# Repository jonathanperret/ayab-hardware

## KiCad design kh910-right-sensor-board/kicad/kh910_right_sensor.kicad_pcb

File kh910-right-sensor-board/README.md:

# KH-910 right-hand sensor board (BP-111025-7 / PCB-E-144)

Reverse-engineering workspace for the Brother KH-910 right sensor board
(3 optical encoders via photo-interrupters PI1/PI2, hall-sensor amplifier
IC303 + comparator, mylar-reader signal conditioning).

- `tracer/` — local interactive tracing tool. Run `python3 tracer/server.py`
  and open http://localhost:8765/. All work is in `tracer/state.json`
  (pads with positions on both photos, traces with side + corners, parts);
  every save keeps a copy in `tracer/backups/`.
- `photos/` — original photos: both sides, crack close-ups, repairs, S-5 connector.
- `images/` — annotated photos, crack/repair maps; `tests/` = continuity-test probe maps.
- `kicad/` — KiCad 10 project. The schematic is the same drawing as `schematic/` (converted element by element by `kicad/build/svg_to_kicad_sch.py`) and its connectivity is checked against the tracer netlist on every build; the PCB uses the tracer's pad positions and tracks (rounded corners), with nets named as in the schematic. `kicad/build/build.sh` regenerates both (needs a python with numpy, scipy and schemdraw: `PYTHON=... kicad/build/build.sh`) and writes `erc_report.txt` / `drc_report.txt`.
- `schematic/` — schematic sheets drawn from the tracer netlist (`draw_schematic.py`), `netlist.txt` at the top level.

## Measured so far (multimeter)
- Harness pad I = +5V, H = GND; D = IC302 p13, E = IC301 p14, F = IC301 p7, G = IC301 p8.
- Bottom harness, two bundles: optical (mylar reader) board on J signal, K GND, L +5V;
  hall sensor board on M +5V, N and P outputs (difference amplifier IC303 via R335/R334), O GND.
- Open solder jumpers (solder side): JP1 between R325.1 and R326.1, JP2 between R323.1 and R324.1.
- Flex cracks repaired 2026-11-15: R1 solder-side GND bus (top edge), R2 +5V
  trace under IC302, R3a/b right-edge +5V trace (both sides), R4 solder jumper.

## To beep when the board is back
- R305.1 ↔ IC301.11 (expect beep: component-side right-edge trace = GND, drawn on that assumption)
- R305.1 ↔ IC301.4 (expect open)
- pad I ↔ IC302.2 (expect open; +5V should be on IC302.3)
- IC301 (324) pins 1, 2, 3, 6, 13 have no solder-side copper; their connections run under the IC body (component side). Beep:
  IC301.6 ↔ IC301.9, IC301.13 ↔ IC301.9 (shared comparator reference?), IC301.1 ↔ IC301.2 (follower?),
  (section 1, pins 1-3, treated as unused).
- Interrupter outputs to comparators: PI1.5 and PI1.6 ↔ IC301.5 / IC301.10 / IC301.12.
- PI1.3 and PI1.7: no copper found, assumed NC; confirm with diode test.
- Hall amplifier (IC303 section 2): IC303.7 ↔ CH301 net (expect beep, via152?). IC303.5 (IN2+) ↔ VR301.3 / R333.2-R335.1 node / pad J (via148):
  tells whether VR301 sets an offset (wiper reaches IN2+) or the hall sensor drive (wiper only feeds pad N).
  Powered test: no magnet near the sensor, turn VR301 and watch CH301 (large smooth change = offset).
- Hall/optical mixing at IC302.11 (IN4+): traces say hall out → R322 → IC302.11 and R321 links IC302.11 to the optical divider (R320/R319).
  Hall and optical must not mix, so something is off. Measure ohms: IC302.11 ↔ pad J (expect open or very high),
  R321.1 ↔ R320.1, R321.2 ↔ R322.2, and confirm which two pads each of R319–R322 actually spans.
- PI1/PI2 LED chain: R303.2, R304.2 ↔ +5V (expect beep); diode test PI1.1→PI1.3 and PI1.2→PI1.4 (~1.1 V), PI1.3 ↔ PI1.4 (beep if tied); PI1.8 ↔ +5V.
- R303.2 / R304.2 supply is not visible on either photo (likely under the resistor bodies, component side): beep R303.2 ↔ R304.2, R304.2 ↔ pad I, R305.2 ↔ R304.2 and ↔ pad I.
  (Repair R4 = jumper bridging the cracked R310.2 → via137 trace.)
- R309.1 ↔ R310.2 (expect 0 Ω: shared reference ladder +5V–R306–R307–R309–R310–GND).
- Links drawn on inference (hidden copper), confirm by beeping: IC302.10 ↔ via152 (hall amp out); R322.1 ↔ IC302.13;
  R318.2 / R320.2 ↔ +5V; via148 (pad J) ↔ IC302.4 and IC302.6; via089 ↔ IC301.4; D301 cathode side ↔ PI1.3/PI1.4/PI2.4;
  R303.2 ↔ IC301.5; R304.2 ↔ IC301.10; D301 band toward PI1.8.

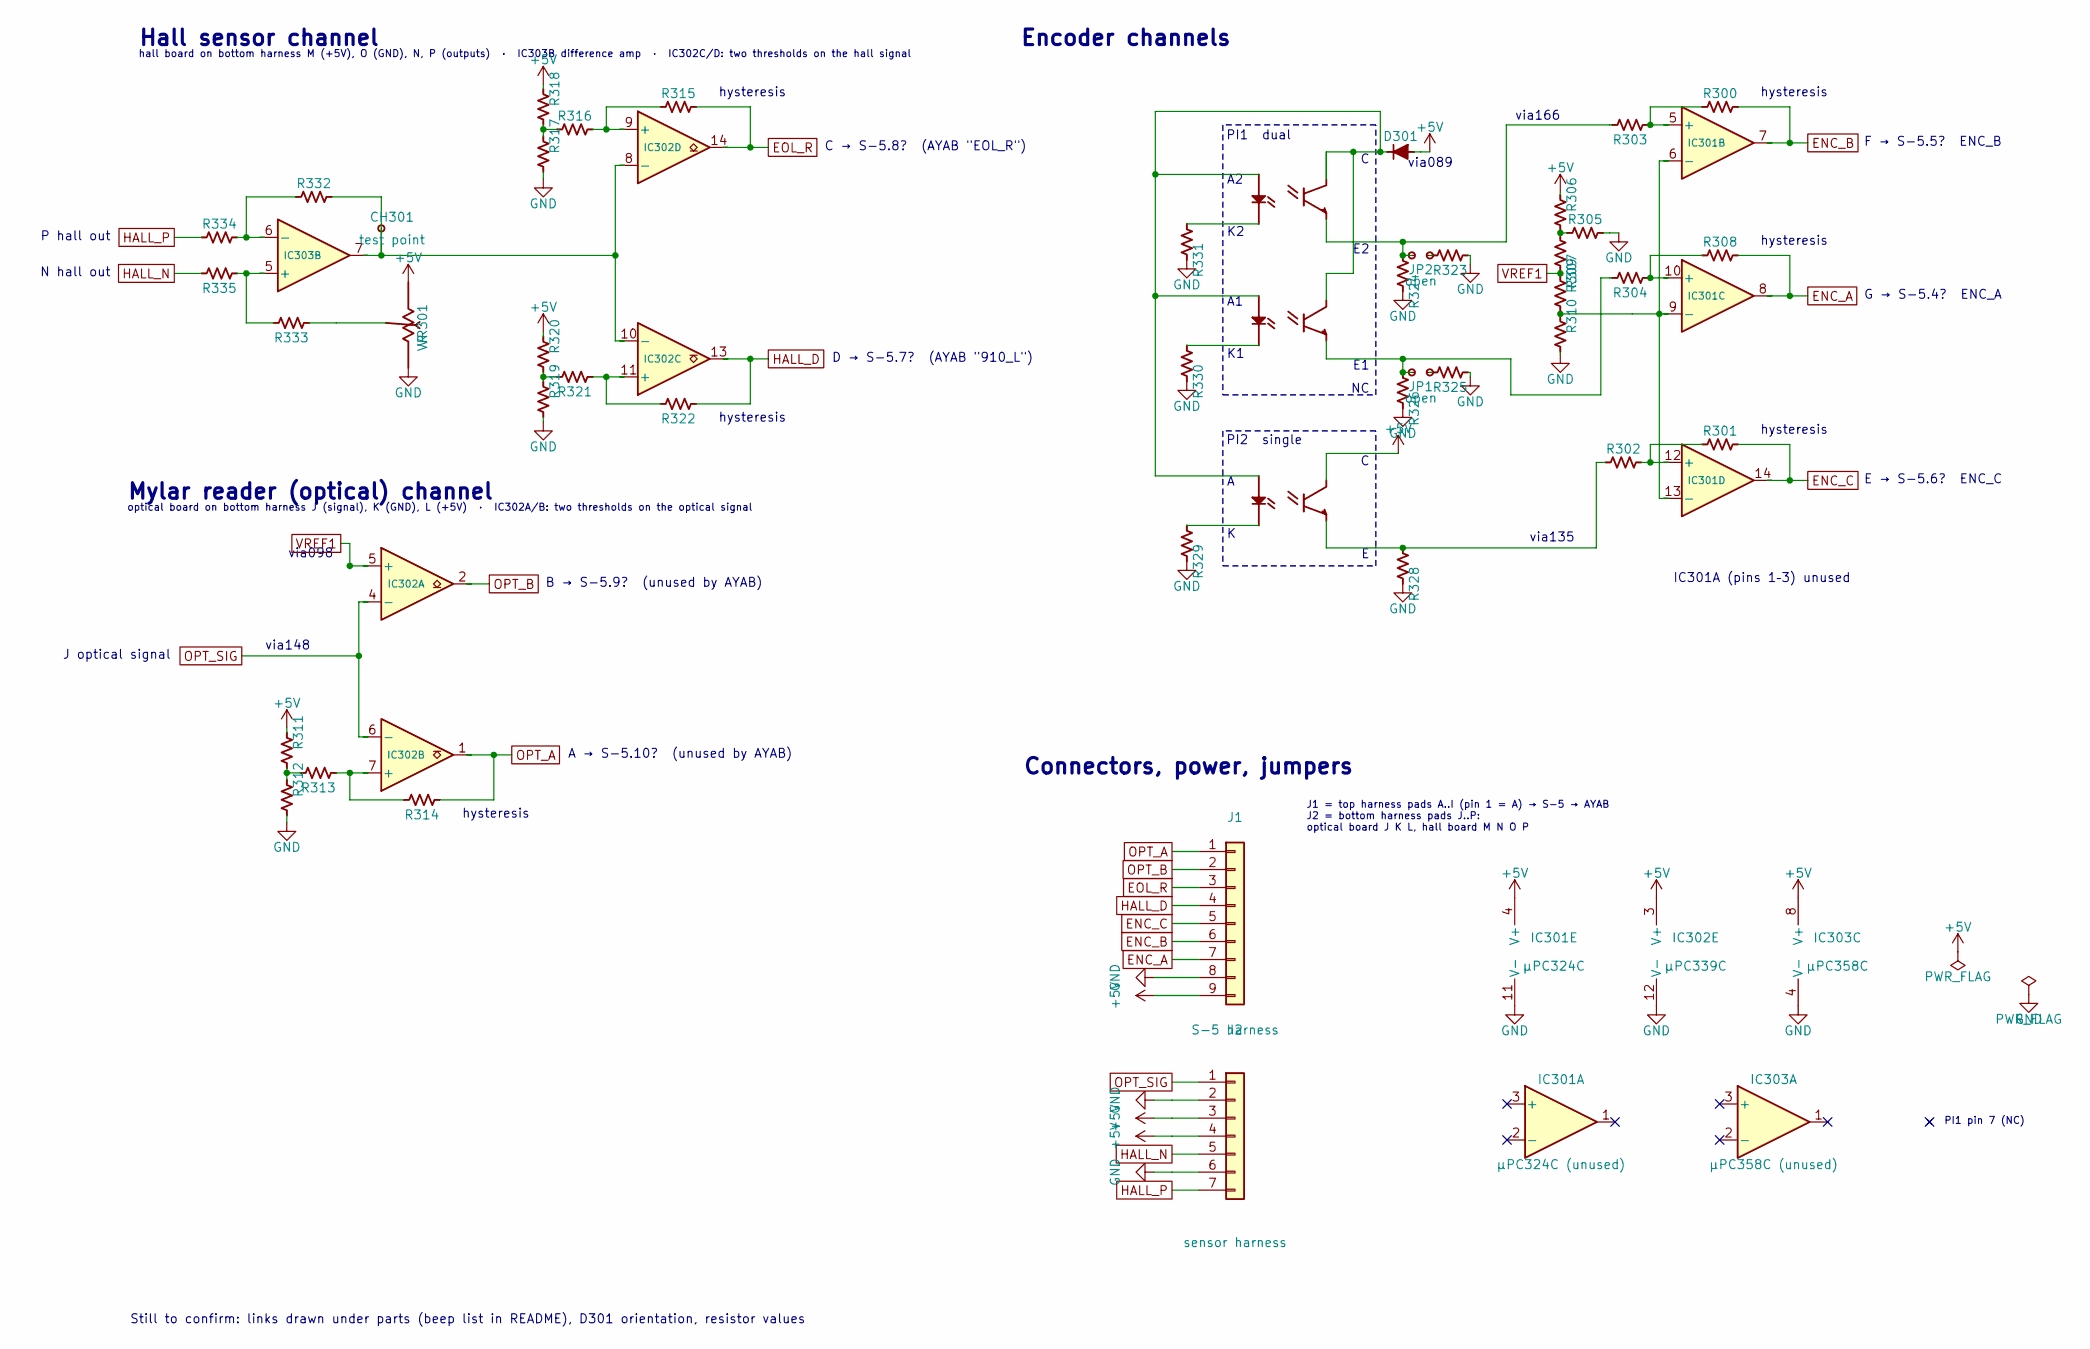
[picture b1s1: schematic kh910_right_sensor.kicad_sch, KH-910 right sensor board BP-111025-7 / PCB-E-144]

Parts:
CH301: test point; CH301
D301: D; D_DO-35_SOD27_P7.62mm_Horizontal
IC301: µPC324C; DIP-14_W7.62mm
IC302: µPC339C; DIP-14_W7.62mm
IC303: µPC358C; DIP-8_W7.62mm
J1: S-5 harness; PinHeader_1x09_P2.54mm_Vertical
J2: sensor harness; PinHeader_1x07_P2.54mm_Vertical
JP1, JP2: open; SolderJumper_open
PI1: PI1
PI2: PI2
R300, R301, R302, R303, R304, R305, R306, R307, R308, R309, R310, R311, R312, R313, R314, R315, R316, R317, R318, R319, R320, R321, R322, R323, R324, R325, R326, R328, R332, R333, R334, R335: R; R_Axial_DIN0204_L3.6mm_D1.6mm_P5.08mm_Horizontal
R329, R330, R331: R; R_Axial_DIN0207_L6.3mm_D2.5mm_P10.16mm_Horizontal
VR301: VR; VR301

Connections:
+5V: D301.2, IC301.4 (V+), IC302.3 (V+), IC303.8 (V+), J1.9, J2.3, J2.4, PI2.1 (C), R306.2, R311.2, R318.2, R320.2, VR301.1
ENC_A: IC301.8, J1.7, R308.2
ENC_B: IC301.7, J1.6, R300.2
ENC_C: IC301.14, J1.5, R301.2
EOL_R: IC302.14, J1.3, R315.2
GND: IC301.11 (V-), IC302.12 (V-), IC303.4 (V-), J1.8, J2.2, J2.6, R305.1, R310.1, R312.1, R317.1, R319.1, R323.2, R324.2, R325.2, R326.2, R328.2, R329.2, R330.2, R331.2, VR301.3
HALL_D: IC302.13, J1.4, R322.1
HALL_N: J2.5, R335.2
HALL_P: J2.7, R334.2
unnamed: IC301.5 (+), R300.1, R303.2
unnamed: IC301.6 (-), IC301.9 (-), IC301.13 (-), R309.1, R310.2
unnamed: IC301.10 (+), R304.2, R308.1
unnamed: IC301.12 (+), R301.1, R302.2
unnamed: IC302.7 (+), R313.1, R314.1
unnamed: IC302.11 (+), R321.2, R322.2
unnamed: CH301.1, CH301.2, IC302.8 (-), IC302.10 (-), IC303.7, R332.1
unnamed: IC302.9 (+), R315.1, R316.1
unnamed: IC303.5 (+), R333.2, R335.1
unnamed: IC303.6 (-), R332.2, R334.1
unnamed: JP1.1, R325.1
unnamed: JP2.1, R323.1
unnamed: D301.1, PI1.3 (A1), PI1.4 (A2), PI1.8 (C), PI2.4 (A)
unnamed: PI1.6 (K2), R331.1
unnamed: JP2.2, PI1.2 (E2), R303.1, R324.1
unnamed: PI1.5 (K1), R330.1
unnamed: JP1.2, PI1.1 (E1), R304.1, R326.1
unnamed: PI2.3 (K), R329.1
unnamed: PI2.2 (E), R302.1, R328.1
unnamed: R305.2, R306.1, R307.1
unnamed: R311.1, R312.2, R313.2
unnamed: R316.2, R317.2, R318.1
unnamed: R319.2, R320.1, R321.1
unnamed: R333.1, VR301.2
OPT_A: IC302.1, J1.1, R314.2
OPT_B: IC302.2, J1.2
OPT_SIG: IC302.4 (-), IC302.6 (-), J2.1
VREF1: IC302.5 (+), R307.2, R309.2

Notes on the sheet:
Hall sensor channel
hall board on bottom harness M (+5V), O (GND), N, P (outputs) · IC303B difference amp · IC302C/D: two thresholds on the hall signal
P hall out
N hall out
C → S-5.8? (AYAB "EOL_R")
hysteresis
D → S-5.7? (AYAB "910_L")
Mylar reader (optical) channel
optical board on bottom harness J (signal), K (GND), L (+5V) · IC302A/B: two thresholds on the optical signal
J optical signal
via148
via098
B → S-5.9? (unused by AYAB)
A → S-5.10? (unused by AYAB)
Encoder channels
PI1 dual
PI2 single
via089
F → S-5.5? ENC_B
G → S-5.4? ENC_A
E → S-5.6? ENC_C
via135
via166
IC301A (pins 1–3) unused
Connectors, power, jumpers
J1 = top harness pads A..I (pin 1 = A) → S-5 → AYAB J2 = bottom harness pads J..P: optical board J K L, hall board M N O P
PI1 pin 7 (NC)
Still to confirm: links drawn under parts (beep list in README), D301 orientation, resistor values

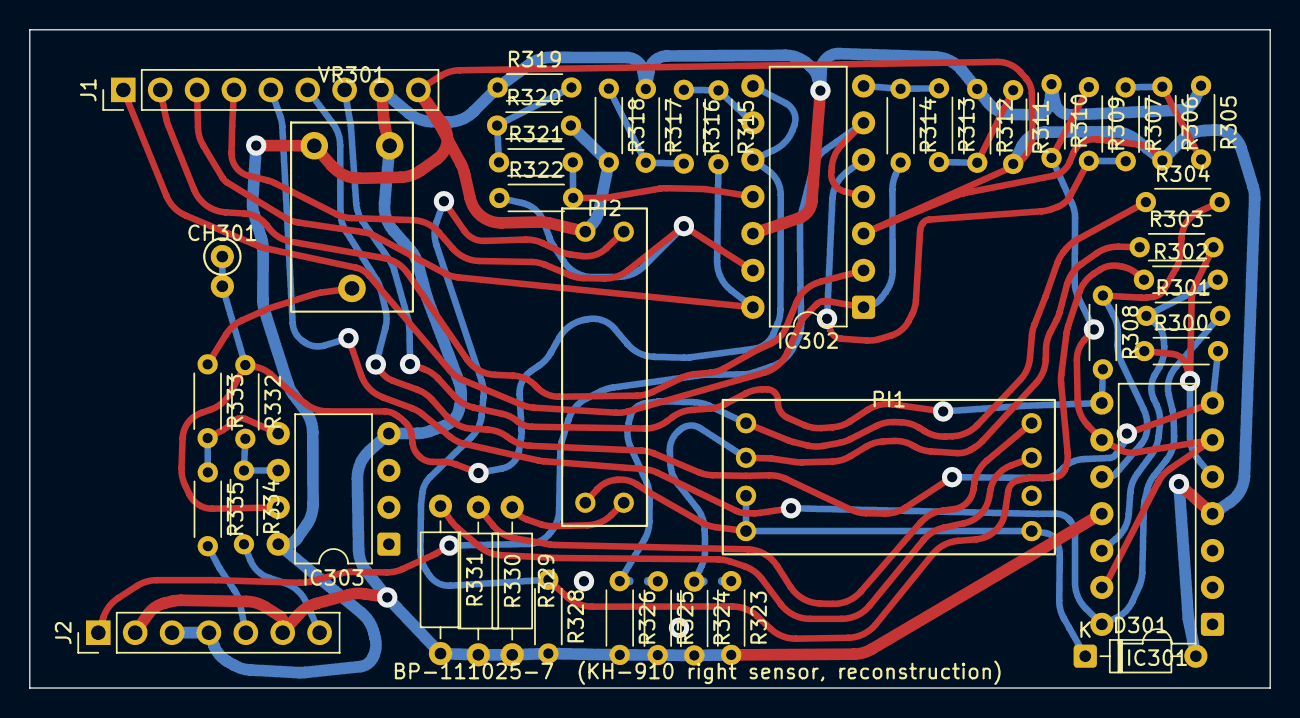
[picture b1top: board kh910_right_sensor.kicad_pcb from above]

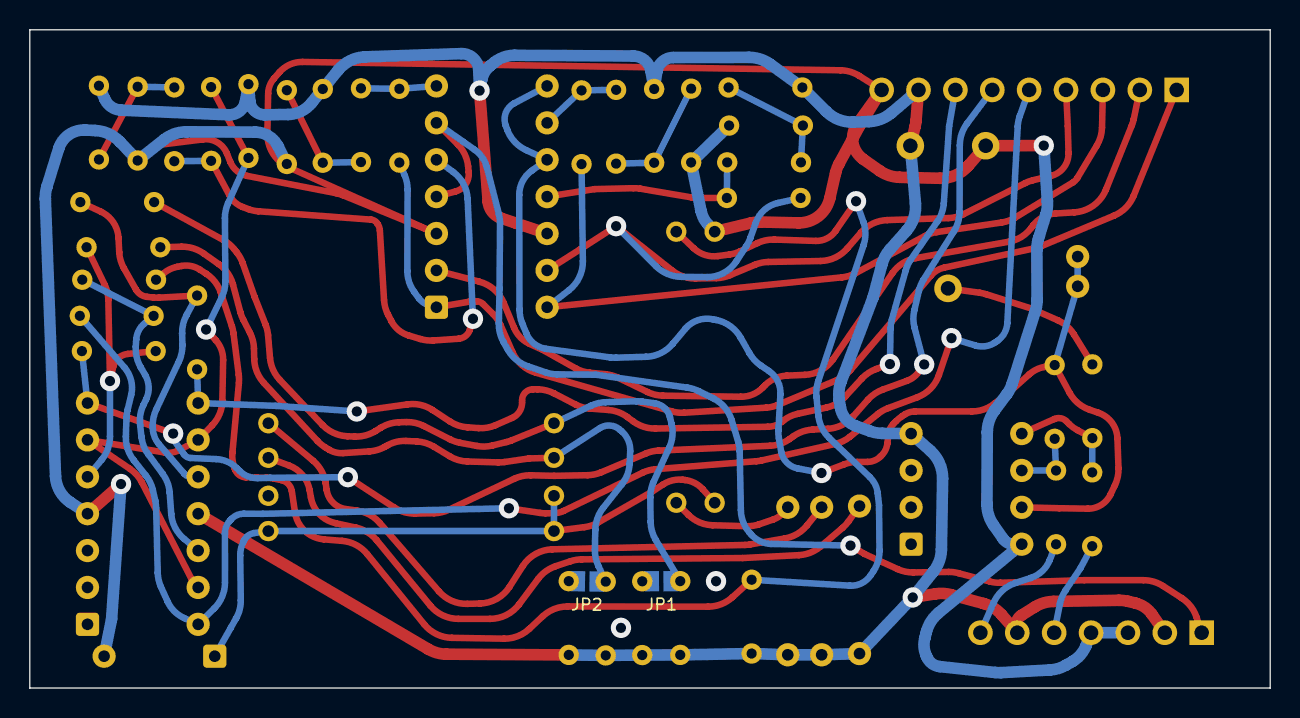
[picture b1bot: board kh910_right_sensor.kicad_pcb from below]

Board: 2 copper layers, 85.4 x 45.3 mm, 47 parts (2 on the bottom side), 37 nets.

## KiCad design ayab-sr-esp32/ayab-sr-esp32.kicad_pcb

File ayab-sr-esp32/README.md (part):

# AYAB-SR-ESP32

ESP32-S3 interface board for Silver Reed knitting machines (successor of the
`ayab-silver-reed-shield` in `silverreed-firmware`). KiCad 10 project.
AYAB talks to it over Wi-Fi in normal use; USB (J2) is the fallback for users
who prefer a cable, and for flashing.

Status: schematic complete, board placed and routed (DRC: 0 unconnected, no
clearance errors). Not built yet — see *Open points* before ordering.

The schematic is a single A2 sheet split into titled sections: power input,
5 V buck, 3.3 V supply, USB (programming), user interface, solenoid buck,
current sense and limiter, mechanical, MCU, level shifting and machine
connector. Sections connect through net labels.

## Power

| Rail | Source | Notes |
|---|---|---|
| `+15V` | J1 USB-C PD, CH224A (U1) asks for 15 V, set by R1 = 56k alone (I²C not used) | Feeds both bucks |
| `Vout` / `Vsol` | U6 TPS54202; Q1 bypasses it (≈ 15 V) until an overcurrent, then it regulates at 8.05 V (R4/R24/R5 = 100k/3.3k/4.7k) | Solenoid supply, through shunt R6 (50 mΩ); `Vsol` goes to the DIN socket |
| `+5V` | U9 TPS54202, R12/R13 = 75k/10k → 5.07 V | Machine logic (DIN pin 7), U4, pull-ups R15–R18 |
| `+3.3V` | U10 AP2112K from `+5V` (D2) or J2 VBUS (D1) | ESP32, OLED, U7, U8 |

- U6 (solenoids) is enabled by the ESP32 (`SOL_EN`, 100k pull-down: off until
  the firmware turns it on). U9 is always on.
- Current limiter: U7 INA381A1 senses R6 (Kelvin connection), compares with
  a fixed threshold, and its `ALERT` output switches Q1, which pulls
  U6's FB to ground. `Vsense` (U7 VOUT, 1 V/A) is read by the ESP32.
  Threshold: R9 82k / R25 10k / R26 7.5k / R23 27k on 3.3 V gives CMPREF
  0.90 V, i.e. 0.90 A (starting values, to be confirmed on the silverreed shield;
  R24 sets the 8 V fallback, R25/R26 the threshold).
  Why 8 V: a solenoid is about 7 Ω cold (a little more once warm), so 0.9 A
  takes 6.3 V across it, plus the VCE of the carriage's Darlington driver and
  the drop in the DIN cable to the carriage.
  Hysteresis 4 µA × (12.5k + R10 82k) ≈ 0.38 V, i.e. ~0.4 A; CMPREF (0.90 V)
  stays above it, so `ALERT` always releases (RESET is tied
  to GND).

## ESP32-S3-WROOM-1 pin map

| GPIO | Module pin | Signal | Direction / notes |
|---|---|---|---|
| IO0 | 27 | `BTN_C` | S1 push (centre); also the BOOT strap: held at reset → download mode |
| IO1 | 39 | `Vsense` | ADC1_CH0, U7 output, 1 V per amp of solenoid current |
| IO2 | 38 | `Vsol_div` | ADC1_CH1, `Vsol` × 10/57 (R7 47k / R8 10k): 15 V → 2.63 V |
| IO8 | 12 | `SDA` | I²C, OLED (U5) only, 4.7k pull-ups R21/R22 |
| IO18 | 11 | `SCL` | I²C |
| IO9 | 17 | `ND1_3V` | Machine ND1 via U8 |
| IO10 | 18 | `CCP_3V` | Machine CCP (carriage clock) via U8 |
| IO11 | 19 | `HOK_3V` | Machine HOK (direction) via U8 |
| IO13 | 21 | `KSL_3V` | Machine KSL (point cam) via U8 |
| IO14 | 22 | `DOB_3V` | Output: solenoid data, to the DIN via U4 (5 V) |
| IO16 | 9 | `BTN_B` | S1 rolled toward the USB-C edge (away from the DIN) |
| IO17 | 10 | `BTN_D` | S1 rolled toward the DIN |
| IO38 | 31 | `SOL_EN` | Output: enable of the solenoid buck U6 (high = on) |
| IO39 | 32 | `PG` | CH224A power-good (open drain, 10k pull-up) |
| IO19/IO20 | 13/14 | USB D−/D+ | Native USB on J2 (through U2 ESD) |
| TXD0/RXD0 | 37/36 | J4 | UART header, not populated by default |

Firmware notes:

- Machine inputs: U8 (74LVC125, powered from 3.3 V, 5 V-tolerant inputs)
  translates the 5 V DIN signals; R15–R18 pull them up to 5 V on the DIN side,
  so `INPUT` is enough on the ESP32 side (no internal pull-up needed).
- `DOB`: U4 (74AHCT1G125 on 5 V) drives the DIN from the 3.3 V GPIO.
- Buttons: S1 common is GND → `INPUT_PULLUP`, active low.
- Avoided on purpose: IO3, IO45, IO46 (straps), IO35–IO37 (PSRAM on some
  module variants).
- The I²C bus is the OLED's only: the CH224A's CFG2/CFG3 are left open
  (single-resistor mode, R1 alone requests 15 V). Unpowered, the CH224A would
  pull them toward its dead supply (internal pull-ups) and hold the bus at
  about 2 V, below the ESP32's and the SSD1306's VIH.
- The ESP32 and the display also run with only J2 plugged in (`+3.3V` from J2
  VBUS through D1 and U10). A PD adapter plugged into J2 instead of J1 can be
  detected: `PG` stays high (the CH224A is unpowered) and no USB host enumerates
  the ESP32.

## Connectors

| Ref | Function |
|---|---|
| J1 | USB-C, power input (USB-PD 15 V) |
| J2 | USB-C, ESP32 native USB (programming, serial) |

J1 and J2 are 14.8 mm apart (centre to centre), like the USB-C ports of a
MacBook, so dual-plug MacBook cables and hubs fit both at once.
| J3 | DIN-7 female, to the knitting machine |
| J14 | 1×8 header duplicating the DIN signals (debug / alternative cable) |
| J4 | ESP32 UART0 (TX, RX), not populated |
| S1 | BL-DT 3-way thumb wheel, wheel protrudes past the top edge, under the OLED. Per the datasheet, rolling the rim 24° toward a terminal's side closes it: toward the USB-C edge → B, toward the DIN → D; push → C (common A to GND) |
| U5 | 0.91" 128×32 I²C OLED module, Hansheng HS91L02W2C01 (LCSC C5248081, SSD1306, address 0x3C), plugged into J15 on its own 2.5 mm pin spacer; any 38 × 12 mm 4-pin GND/VCC/SCL/SDA module fits. Not in the JLCPCB BOM nor the CPL: bought separately and fitted at assembly (see *Assembly-time parts*). Its far end overhangs the board edge and rests on a block of the enclosure tray |
| J15 | Low-profile 1×4 2.54 mm female socket for U5, 5.0 mm high (HC-PM254-5.0H-1x4PZ-02A, LCSC C42163122; standard sockets are 8.5 mm) |

DIN J3 and J14 pinout:

| Signal | J3 | J14 |
|---|---|---|
| ND1 | 1 | 2 |
| KSL | 2 | 3 |
| DOB | 3 | 4 |
| CCP | 4 | 5 |
| HOK | 5 | 6 |
| Vsol | 6 | 7 |
| +5V | 7 | 8 |
| GND | shield (8) | 1 |

## PCB

- 2 layers, GND pour on both sides, 64.5 × 97.1 mm (width × height), drawn in
  its intended orientation: DIN socket J3 facing up, USB-C sockets on the
  right edge. A 23.9 × 8.7 mm notch above the DIN socket leaves room for bulky
  plugs. S1's wheel sticks out of the top edge, centred on its straight part
  (x 123.9–164.5 before the antenna-side cut, see below); the OLED's visible area sits 0.5 mm further from the DIN
  than S1's axis (the HS91L02W2C01 active area is 7.62 mm from the end of
  its board, not the 7.1 mm the board was laid out for).
- Net classes: Power 0.6 mm (`+15V`, U6 switch node, `Vout`, `Vsol`),
  Supply 0.3 mm (`+5V`, `+3.3V`, LDO input, J2 VBUS), Default 0.2 mm.
- Minimum track 0.15 mm (fine-pitch escapes), minimum hole 0.2 mm (ESP32
  footprint thermal vias): within JLCPCB's standard process.
- Antenna: the ESP32 antenna is on the right edge, with a 5.6 × 47.9 mm
  cut-out under it (y 38.7–86.6, from x = 158.9: the keep-out starts at
  158.66, the 0.24 mm strip left keeps the SDA/SCL tracks 0.5 mm from the
  edge). The board was lengthened by 6 mm at the bottom so that the OLED
  module clears the keep-out: the top components (J3, U5, S1) and the top
  edge stayed in place, everything else moved down 6 mm (U5's courtyard ends
  at y 38.55, the keep-out starts at 38.7). Above the cut-out, the board is
  cut along the same line (x = 158.9) up to the top edge: the far end of the
  OLED module overhangs the board there by 5 mm and rests on a block of the
  enclosure tray. The board was then lengthened by 8 mm more at the bottom
  (nothing moved but the bottom edge and the holes).
- Mounting holes (M3, GND pad): H1 and H3 in the two bottom corners, 5.4 mm
  from the side edges and 5.3 mm from the bottom (105.4 / 116.8 and
  159.1 / 116.8), and H2 below the OLED near the right edge (155.4 / 44.5: as far
  right as the antenna keep-out allows, its lid column 2.9 mm from the OLED module).
- Routing: [UltraRoute](https://github.com/sequoia-hope/ultraroute) (commit `ddc2375`), following
  the phase-7 method of [Boardroom](https://github.com/sequoia-hope/boardroom)'s design skill,
  adapted to 2 layers and kept to 0/45/90-degree tracks. It lays the board out from bare pads, so a
  re-route is reproducible:
  - Before routing: the mechanically fixed parts locked (J1–J3, J15, U5, S1, U3, H1–H3); the GND
    pour on B.Cu only, as a soft plane (crossing it costs, `--pour-cost 3`); a GND via at every
    SMD ground pad; short links drawn from pad positions: the Kelvin pair from the inner side of
    shunt R6's pads to U7, and 0.5 mm stubs out of J1's VBUS pads; edge strips (no tracks or vias,
    pours allowed) between the USB-C, DIN and J14 pads and the board edge.
  - Rules in `ayab-sr-esp32.kicad_dru`, which both the router and KiCad's DRC apply: Power class
    at least 0.4 mm (0.6 where there is room), Supply at least 0.25 mm (0.3), except the Kelvin
    tracks inside the `kelvin-u7` area.
  - Router stages: UltraRoute's default recipe without `--tighten` (which pulls the copper taut at
    any angle) and without `--diff-pairs` (its coupled pairs are laid at any angle too; the ESP32-S3's
    USB is full-speed only, about 40 mm here, and needs no coupled routing):
    `--negotiate --rip-up --rip-boxed --prefanout --escape-room --shove-plough region --shove-reach 0.5
    --shove-repair 20 --shove-ties --guard-ties --shove-passes 60 --shove-patience 8 --strip
    --pour-cost 3 --seed N --threads 1 --timeout 240`, nice'd, one run at a time.
  - Seeds 0–9 tried, each judged by KiCad after restoring the F.Cu pour and refilling (all clean);
    seed 9 kept for its short 15 V buck switch node (11.1 mm, no via) and bootstrap (1.9 mm, no
    via: C4 sits beside U6, its pads 2.7 mm from BOOT and 3.6 mm from SW).
  - After routing: GND pours on both sides, stitching vias on a 3 mm grid, dangling copper
    removed, all copper unlocked (only the parts above stay locked); then `octofix.py` turns every
    segment off a multiple of 45 degrees into a 45-degree leg and an orthogonal leg (ends unmoved,
    the variant KiCad's DRC accepts), and collinear pieces are merged. 99.7% of the track length is
    at 0/45/90 degrees; what is left is 32 pad entries of at most 0.3 mm and 2 short jogs.
  - Checks: DRC 0 errors and 0 unconnected with every severity on (`min_connection` 0.127 mm;
    dangling tracks and vias, slivers, isolated copper and connection width as errors); every pad's
    best joint at least min(0.15 mm, track width); B.Cu ground in one piece (5138 mm²), stitched to
    the F.Cu pour.
  - Against the Freerouting route: 2093 mm of track instead of 2059 mm, 79 signal and power
    vias plus 452 GND vias (45 at ground pads, the rest stitching), B.Cu ground in 1 piece instead of 14, and power tracks at
    their class widths (the old route had 90 power tracks under them).
  - The driver and the board's routing inputs are on the `tooling` branch
    (`scripts/kicad/route/ultraroute/`, `ayab-sr-esp32/tools/ultraroute/`): `route.sh ayab-sr-esp32 WORK 9`,
    then `finish.sh WORK/j9 WORK/final`, regenerates this board.
  - Placement finding: J1's VBUS pads sit between the CC pins, so its stubs are 0.5 mm, not 0.6.

3D models: `ayab-library/packages3D/OLED_0.91_128x32_I2C.step` (generated by
`packages3D/generators/oled_0.91_128x32_step.py`, raised 5 mm by the U5 footprint for the socket),
`PinSocket_1x04_P2.54mm_Vertical_H5.0.step` for J15 (`packages3D/generators/pin_socket_1x04_h5_step.py`) and `SW-SMD_BL-DT.step` for S1 (CadQuery,
`packages3D/generators/sw_smd_bl_dt_step.py`, from the manufacturer's drawing).

A 3D-printable enclosure is in [`enclosure/`](enclosure/README.md).
Its model follows the board's 90° turn (`board_frame()` in the .scad), the
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
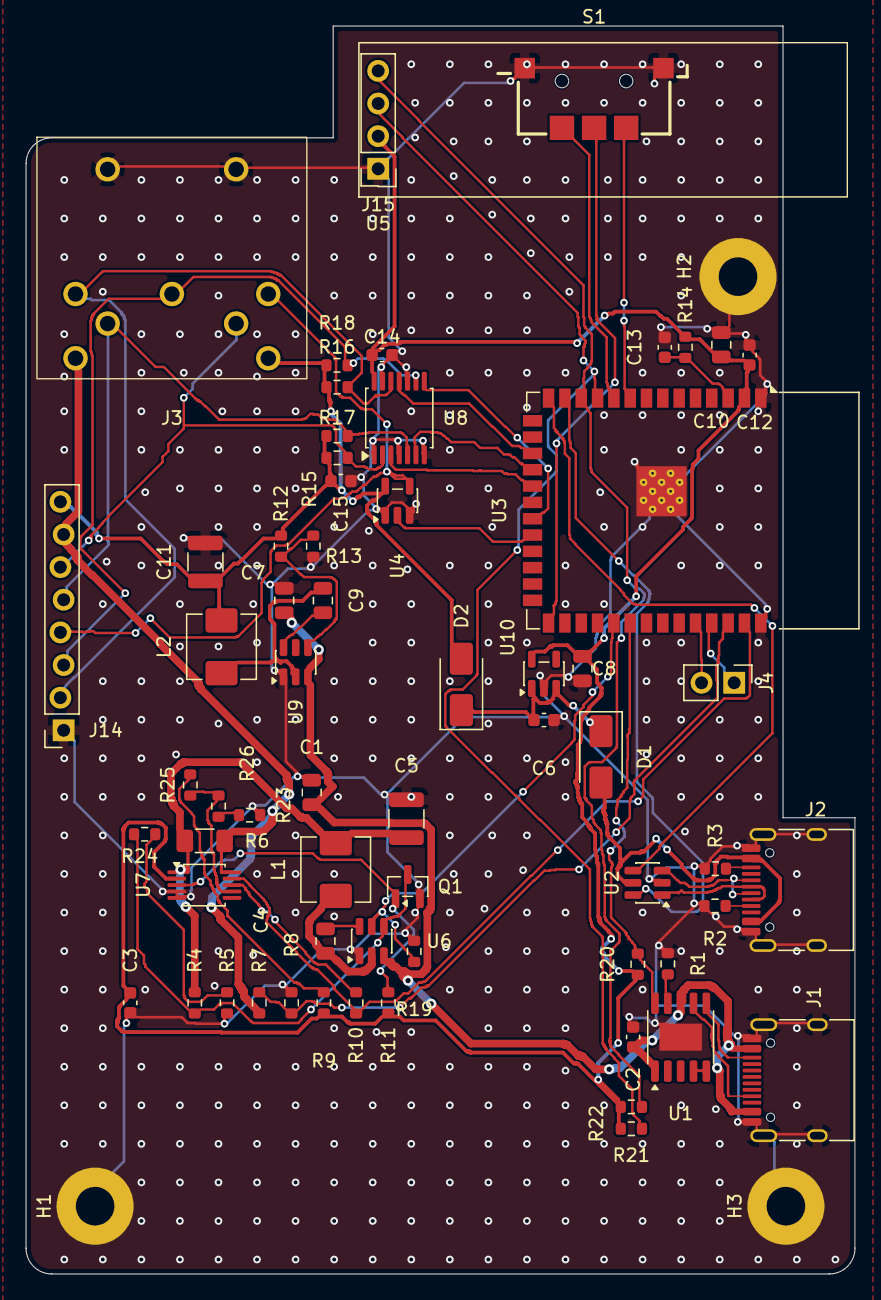
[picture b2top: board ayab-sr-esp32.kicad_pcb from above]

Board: 2 copper layers, 64.5 x 97.1 mm, 66 parts (0 on the bottom side), 52 nets.

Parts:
C1, C7, C8: 10u; C_0805_2012Metric
C2, C6, C13: 1u; C_0603_1608Metric
C3, C12, C14, C15: 100n; C_0603_1608Metric
C4, C9: 100n; C_0805_2012Metric
C5, C11: 47u; C_1210_3225Metric
C10: 22u; C_0805_2012Metric
D1, D2: SS34; D_SMA
H1, H2, H3: MountingHole_Pad; MountingHole_3mm_Pad
J1, J2: USB_C_Receptacle_USB2.0_16P; USB_C_Receptacle_HRO_TYPE-C-31-M-12
J3: DIN-7; DIN-704-M10
J4: Conn_01x02; PinHeader_1x02_P2.54mm_Vertical
J14: Conn_01x08; PinSocket_1x08_P2.54mm_Vertical_Lock
J15: HC-PM254-5.0H-1x4PZ-02A; PinSocket_1x04_P2.54mm_Vertical_H5.0
L1, L2: 10u; L_Changjiang_FXL0518
Q1: BSS138; SOT-23
R1: 56k; R_0603_1608Metric
R2, R3: 5.1k; R_0603_1608Metric
R4, R19: 100k; R_0603_1608Metric
R5, R21, R22: 4.7k; R_0603_1608Metric
R6: 50m; R_1206_3216Metric_Pad1.30x1.75mm_HandSolder
R7: 47k; R_0603_1608Metric
R8, R11, R13, R14, R15, R16, R17, R18, R20, R25: 10k; R_0603_1608Metric
R9, R10: 82k; R_0603_1608Metric
R12: 75k; R_0603_1608Metric
R23: 27k; R_0603_1608Metric
R24: 3.3k; R_0603_1608Metric
R26: 7.5k; R_0603_1608Metric
S1: BL-DT; SW-SMD_BL-DT
U1: CH224A; SSOP-10-1EP_3.9x4.9mm_P1mm_EP2.1x3.3mm
U2: USBLC6-2SC6; SOT-23-6
U3: ESP32-S3-WROOM-1
U4: 74AHCT1G125; SOT-23-5
U5: HS91L02W2C01; OLED_0.91_128x32_I2C_Module_Socket_H5.0
U6, U9: TPS54202; SOT-23-6
U7: INA381A1; TSSOP-10_3x3mm_P0.5mm
U8: 74LVC125; TSSOP-14_4.4x5mm_P0.65mm
U10: AP2112K-3.3; SOT-23-5

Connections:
+3.3V: C3.2, C8.1, C10.1, C12.1, C14.1, J15.2, R9.1, R11.1, R14.1, R20.1, R21.1, R22.1, U3.2 (3V3), U7.2 (VS), U8.14 (VCC), U10.5 (VOUT)
+5V: C11.1, C15.2, D2.2 (A), J3.7, J14.8, L2.2, R12.2, R15.1, R16.1, R17.1, R18.1, U4.5 (VCC)
+15V: C1.1, C2.1, C7.1, J1.A4 (VBUS), J1.A9 (VBUS), J1.B4 (VBUS), J1.B9 (VBUS), U1.1 (VHV), U1.8 (VBUS), U6.3 (VIN), U9.3 (VIN)
/ALERT: Q1.1 (G), R11.2, U7.3 (~ALERT)
/BTN_B: S1.B, U3.9 (IO16)
/BTN_C: S1.C, U3.27 (IO0)
/BTN_D: S1.D, U3.10 (IO17)
/CCP: J3.4, J14.5, R17.2, U8.5 (2A)
/CCP_3V: U3.18 (IO10), U8.6 (2Y)
/CFG1: R1.1, U1.9 (CFG1)
/CMPREF: R25.2, R26.1, U7.7 (CMPREF)
/DOB: J3.3, J14.4, U4.4
/DOB_3V: U3.22 (IO14), U4.2
/FB: Q1.3 (D), R4.1, R24.1, U6.4 (FB)
/HOK: J3.5, J14.6, R15.2, U8.2 (1A)
/HOK_3V: U3.19 (IO11), U8.3 (1Y)
/KSL: J3.2, J14.3, R16.2, U8.9 (3A)
/KSL_3V: U3.21 (IO13), U8.8 (3Y)
/ND1: J3.1, J14.2, R18.2, U8.12 (4A)
/ND1_3V: U3.17 (IO9), U8.11 (4Y)
/PG: R20.2, U1.10 (PG), U3.32 (IO39)
/SCL: J15.3, R22.2, U3.11 (IO18)
/SDA: J15.4, R21.2, U3.12 (IO8)
/SOL_EN: R19.1, U3.31 (IO38), U6.5 (EN)
/USB2_VBUS: D1.2 (A), J2.A4 (VBUS), J2.A9 (VBUS), J2.B4 (VBUS), J2.B9 (VBUS), U2.5 (VBUS)
/USB_DM: U2.6 (I/O1), U3.13 (USB_D-)
/USB_DP: U2.4 (I/O2), U3.14 (USB_D+)
/Vout: C5.1, L1.2, R4.2, R6.1, U7.1 (IN+)
/Vsense: R10.1, U3.39 (IO1), U7.9 (VOUT)
/Vsol: J3.6, J14.7, R6.2, R7.1, U7.10 (IN-)
/Vsol_div: R7.2, R8.1, U3.38 (IO2)
GND: C1.2, C2.2, C3.1, C5.2, C6.2, C7.2, C8.2, C10.2, C11.2, C12.2, C13.2, C14.2, C15.1, H1.1 (1_1), H2.1 (1_1), H3.1 (1_1), J1.A1 (GND), J1.A12 (GND), J1.B1 (GND), J1.B12 (GND), J1.SH (SHIELD), J2.A1 (GND), J2.A12 (GND), J2.B1 (GND), J2.B12 (GND), J2.SH (SHIELD), J3.8 (GND_8), J14.1, J15.1, Q1.2 (S), R1.2, R2.2, R3.2, R5.1, R8.2, R13.1, R19.2, R23.2, S1.A, U1.11 (GND), U2.2 (GND), U3.1 (GND), U3.40 (GND), U3.41 (GND), U4.1, U4.3 (GND), U6.1 (GND), U7.4 (RESET), U7.5 (GND), U8.1 (~1OE), U8.4 (~2OE), U8.7 (GND), U8.10 (~3OE), U8.13 (~4OE), U9.1 (GND), U10.2 (GND)
unnamed: C6.1, D1.1 (K), D2.1 (K), U10.1 (VIN), U10.3 (EN)
unnamed: J1.A5 (CC1), U1.7 (CC1)
unnamed: J1.B5 (CC2), U1.6 (CC2)
unnamed: J2.A5 (CC1), R2.1
unnamed: J2.B5 (CC2), R3.1
unnamed: J2.A6 (D+), J2.B6 (D+), U2.3 (I/O2)
unnamed: J2.A7 (D-), J2.B7 (D-), U2.1 (I/O1)
unnamed: J4.1, U3.37 (TXD0)
unnamed: J4.2, U3.36 (RXD0)
unnamed: R23.1, R26.2
unnamed: R5.2, R24.2
unnamed: R9.2, R25.1
unnamed: U1.4 (DP), U1.5 (DM)
unnamed: C13.1, R14.2, U3.3 (EN)
unnamed: C4.1, U6.6 (BOOT)
unnamed: C4.2, L1.1, U6.2 (SW)
unnamed: R10.2, U7.8 (CMPIN)
unnamed: C9.1, U9.6 (BOOT)
unnamed: R12.1, R13.2, U9.4 (FB)
unnamed: C9.2, L2.1, U9.2 (SW)

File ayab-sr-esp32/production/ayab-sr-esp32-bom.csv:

"Designator","Value","Footprint","LCSC","Qty","DNP"
"C1,C7,C8","10u","Capacitor_SMD:C_0805_2012Metric","C15850","3",""
"C2,C6,C13","1u","Capacitor_SMD:C_0603_1608Metric","C15849","3",""
"C3,C12,C14,C15","100n","Capacitor_SMD:C_0603_1608Metric","C14663","4",""
"C4,C9","100n","Capacitor_SMD:C_0805_2012Metric","C49678","2",""
"C5,C11","47u","Capacitor_SMD:C_1210_3225Metric","C7432791","2",""
"C10","22u","Capacitor_SMD:C_0805_2012Metric","C45783","1",""
"D1,D2","SS34","Diode_SMD:D_SMA","C8678","2",""
"J1,J2","USB_C_Receptacle_USB2.0_16P","Connector_USB:USB_C_Receptacle_HRO_TYPE-C-31-M-12","C165948","2",""
"J3","DIN-7","Library:DIN-704-M10","C20611695","1",""
"J15","HC-PM254-5.0H-1x4PZ-02A","Library:PinSocket_1x04_P2.54mm_Vertical_H5.0","C42163122","1",""
"L1,L2","10u","Inductor_SMD:L_Changjiang_FXL0518","C475910","2",""
"Q1","BSS138","Package_TO_SOT_SMD:SOT-23","C7420339","1",""
"R1","56k","Resistor_SMD:R_0603_1608Metric","C23206","1",""
"R2,R3","5.1k","Resistor_SMD:R_0603_1608Metric","C23186","2",""
"R4,R19","100k","Resistor_SMD:R_0603_1608Metric","C25803","2",""
"R5,R21,R22","4.7k","Resistor_SMD:R_0603_1608Metric","C23162","3",""
"R6","50m","Resistor_SMD:R_1206_3216Metric_Pad1.30x1.75mm_HandSolder","C127691","1",""
"R7","47k","Resistor_SMD:R_0603_1608Metric","C25819","1",""
"R8,R11,R13,R14,R15,R16,R17,R18,R20,R25","10k","Resistor_SMD:R_0603_1608Metric","C25804","10",""
"R9,R10","82k","Resistor_SMD:R_0603_1608Metric","C23254","2",""
"R12","75k","Resistor_SMD:R_0603_1608Metric","C23242","1",""
"R23","27k","Resistor_SMD:R_0603_1608Metric","C22967","1",""
"R24","3.3k","Resistor_SMD:R_0603_1608Metric","C22978","1",""
"R26","7.5k","Resistor_SMD:R_0603_1608Metric","C23234","1",""
"S1","BL-DT","Library:SW-SMD_BL-DT","C53223909","1",""
"U1","CH224A","Package_SO:SSOP-10-1EP_3.9x4.9mm_P1mm_EP2.1x3.3mm","C42459160","1",""
"U2","USBLC6-2SC6","Package_TO_SOT_SMD:SOT-23-6","C2687116","1",""
"U3","ESP32-S3-WROOM-1","RF_Module:ESP32-S3-WROOM-1","C2913198","1",""
"U4","74AHCT1G125","Package_TO_SOT_SMD:SOT-23-5","C52140417","1",""
"U6,U9","TPS54202","Package_TO_SOT_SMD:SOT-23-6","C191884","2",""
"U7","INA381A1","Package_SO:TSSOP-10_3x3mm_P0.5mm","C1849472","1",""
"U8","74LVC125","Package_SO:TSSOP-14_4.4x5mm_P0.65mm","C54411083","1",""
"U10","AP2112K-3.3","Package_TO_SOT_SMD:SOT-23-5","C22365427","1",""

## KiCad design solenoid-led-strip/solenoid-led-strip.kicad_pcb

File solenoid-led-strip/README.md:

# Solenoid LED strip for Brother electronic knitting machines

This board is meant to be used as a debugging aid when working on alternative electronics for the Brother KH-9xx series, such as [AYAB](https://github.com/AllYarnsAreBeautiful). But as it simply inserts itself between the electronics and the solenoids, it can also be used with the machine's original electronics, to understand how they drive the solenoids.

I have not built the board described by this KiCad project yet, only a prototype from the schematic. No guarantee of any kind is offered as to the suitability of these files for producing a working device.

## Prototype board

This board I built uses the same schematic:

## Mockup

## Schematic

## Tracks

## [Interactive view](https://kicanvas.org/?github=https%3A%2F%2Fgithub.com%2Fjonathanperret%2Fayab-hardware%2Ftree%2Fsolenoid-led-strip%2Fsolenoid-led-strip) courtesy of [KiCanvas](https://kicanvas.org)

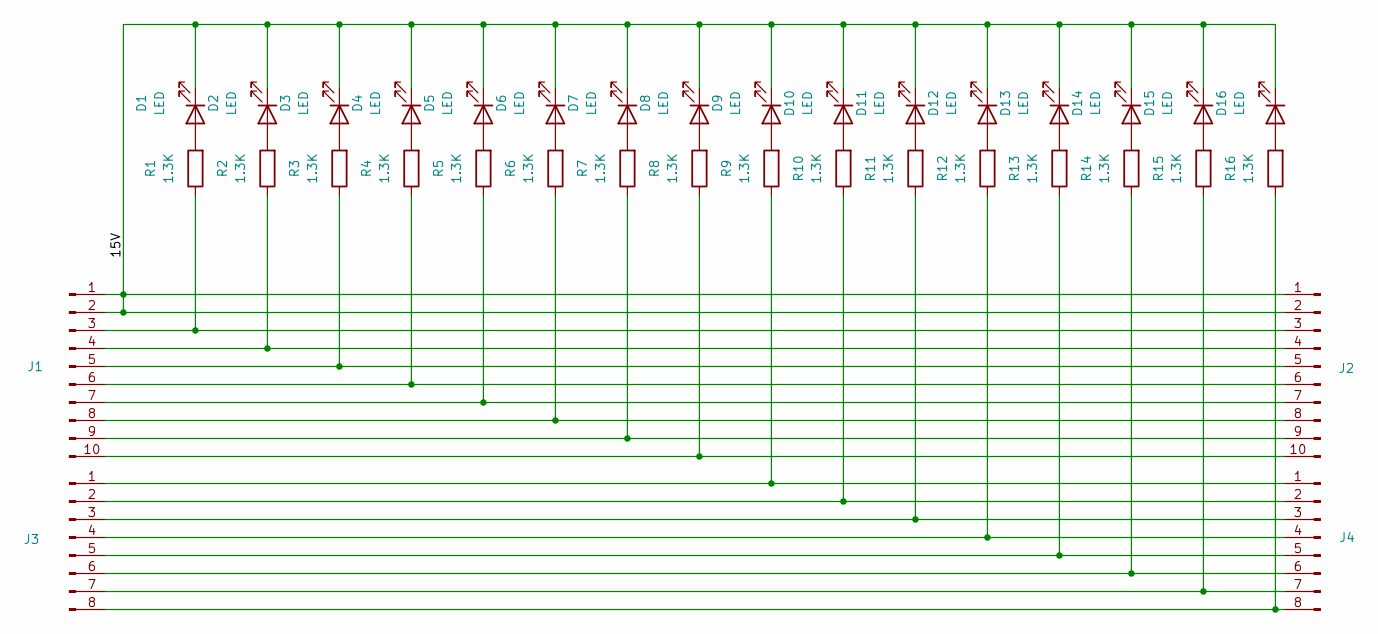
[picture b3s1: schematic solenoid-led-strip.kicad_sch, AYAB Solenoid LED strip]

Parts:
D1, D2, D3, D4, D5, D6, D7, D8, D9, D10, D11, D12, D13, D14, D15, D16: LED; LED_0805_2012Metric
J1: PinHeader_1x10_P2.54mm_Vertical
J2: PinHeader_1x10_P2.54mm_Horizontal
J3: PinHeader_1x08_P2.54mm_Vertical
J4: PinHeader_1x08_P2.54mm_Horizontal
R1, R2, R3, R4, R5, R6, R7, R8, R9, R10, R11, R12, R13, R14, R15, R16: 1.3K; R_0805_2012Metric

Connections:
/15V: D1.1 (K), D2.1 (K), D3.1 (K), D4.1 (K), D5.1 (K), D6.1 (K), D7.1 (K), D8.1 (K), D9.1 (K), D10.1 (K), D11.1 (K), D12.1 (K), D13.1 (K), D14.1 (K), D15.1 (K), D16.1 (K), J1.1, J1.2, J2.1, J2.2
unnamed: D1.2 (A), R1.2
unnamed: D2.2 (A), R2.2
unnamed: D3.2 (A), R3.2
unnamed: D4.2 (A), R4.2
unnamed: D5.2 (A), R5.2
unnamed: D6.2 (A), R6.2
unnamed: D7.2 (A), R7.2
unnamed: D8.2 (A), R8.2
unnamed: D9.2 (A), R9.2
unnamed: D10.2 (A), R10.2
unnamed: D11.2 (A), R11.2
unnamed: D12.2 (A), R12.2
unnamed: D13.2 (A), R13.2
unnamed: D14.2 (A), R14.2
unnamed: D15.2 (A), R15.2
unnamed: D16.2 (A), R16.2
unnamed: J1.3, J2.3, R1.1
unnamed: J1.4, J2.4, R2.1
unnamed: J1.5, J2.5, R3.1
unnamed: J1.6, J2.6, R4.1
unnamed: J1.7, J2.7, R5.1
unnamed: J1.8, J2.8, R6.1
unnamed: J1.9, J2.9, R7.1
unnamed: J1.10, J2.10, R8.1
unnamed: J3.1, J4.1, R9.1
unnamed: J3.2, J4.2, R10.1
unnamed: J3.3, J4.3, R11.1
unnamed: J3.4, J4.4, R12.1
unnamed: J3.5, J4.5, R13.1
unnamed: J3.6, J4.6, R14.1
unnamed: J3.7, J4.7, R15.1
unnamed: J3.8, J4.8, R16.1

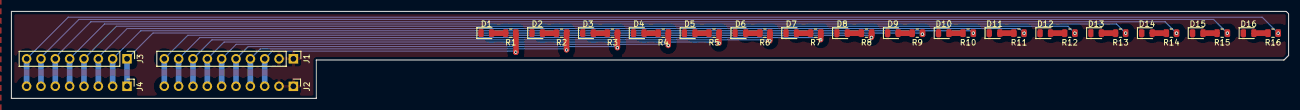
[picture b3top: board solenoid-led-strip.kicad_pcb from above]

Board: 2 copper layers, 226.2 x 15.4 mm, 36 parts (0 on the bottom side), 33 nets.

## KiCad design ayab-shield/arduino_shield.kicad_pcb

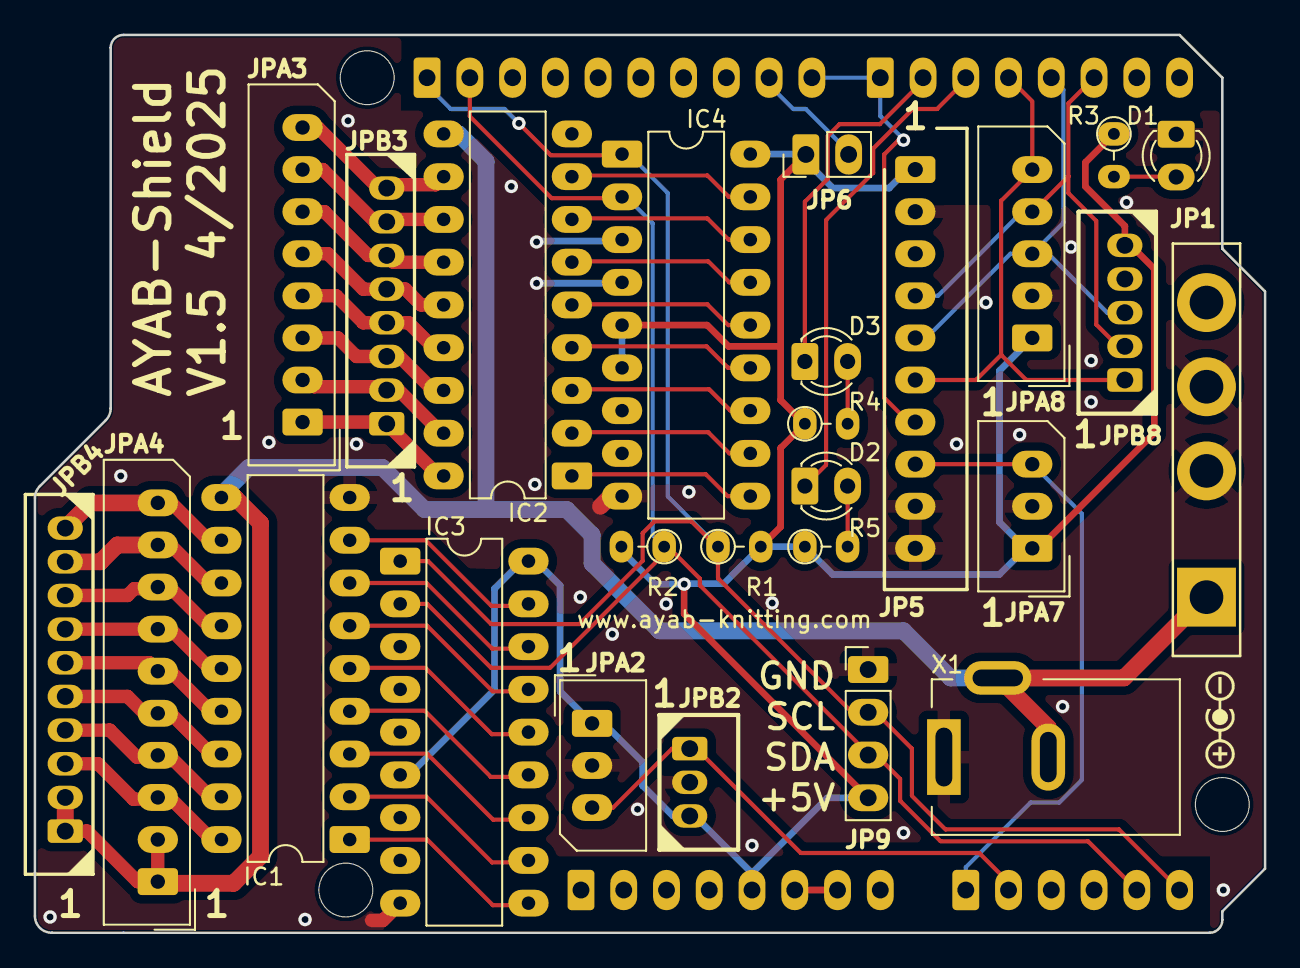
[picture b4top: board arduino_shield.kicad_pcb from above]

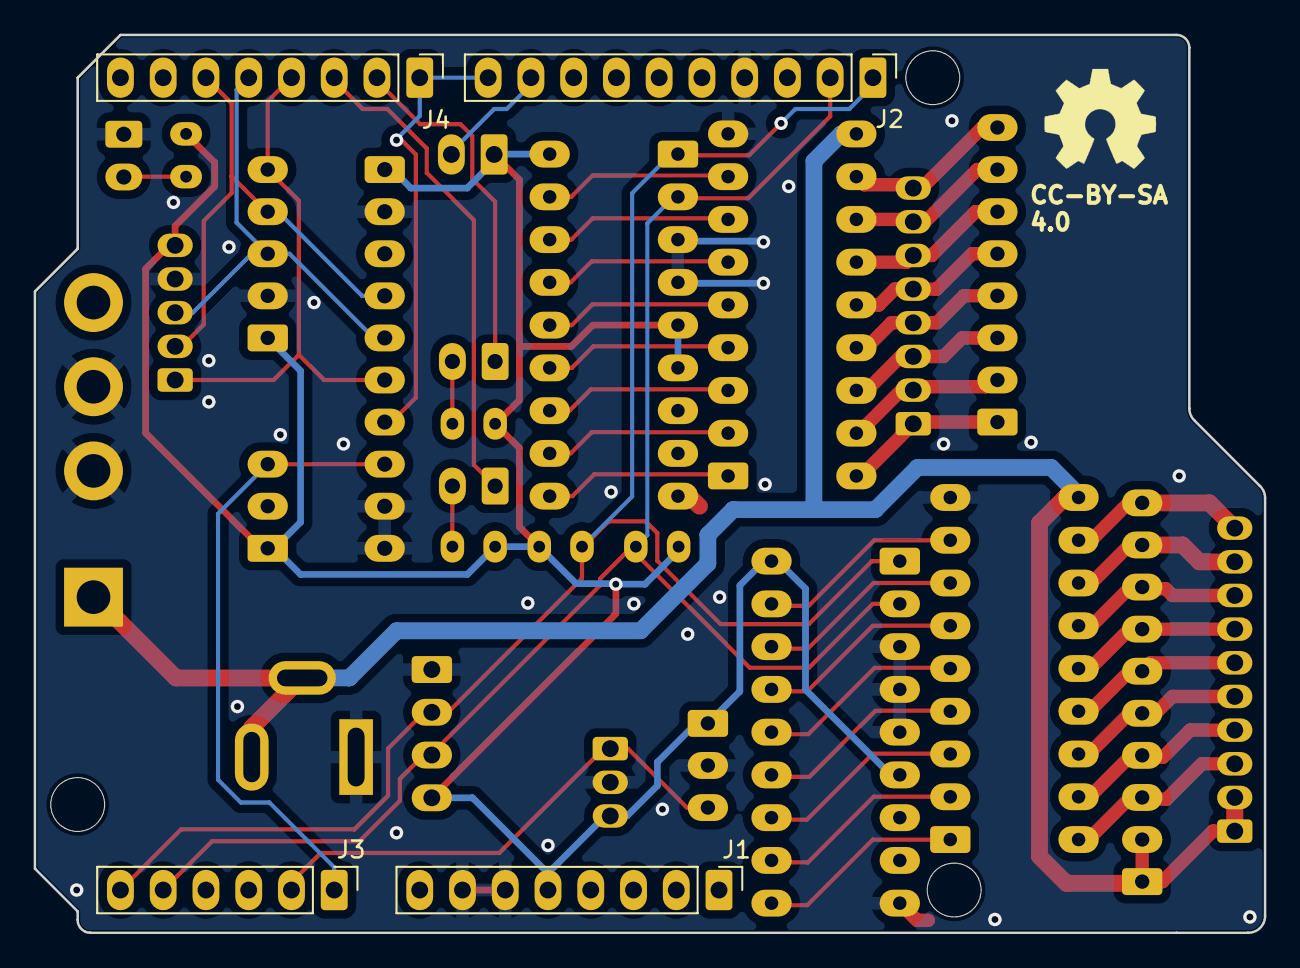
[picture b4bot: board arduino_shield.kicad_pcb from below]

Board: 2 copper layers, 73.1 x 53.3 mm, 33 parts (4 on the bottom side), 49 nets.

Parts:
D1: RED_3MM; LED_D3.0mm
D2: YEL_3MM; LED_D3.0mm
D3: GRN_3MM; LED_D3.0mm
IC1, IC2: ULN2803A; DIP-18_W7.62mm_LongPads
IC3, IC4: MCP2300X/P; DIP-18_W7.62mm_LongPads
J1: Power; PinHeader_1x08_P2.54mm_Vertical
J2: Digital/PWM; PinHeader_1x10_P2.54mm_Vertical
J3: Analog; PinHeader_1x06_P2.54mm_Vertical
J4: Digital/PWM; PinHeader_1x08_P2.54mm_Vertical
JP1: BROTHER POWER; Brother_4P
JP5: 1X10 2.5mm; SHDR10W70P0X250_1X10_2740X490X590P
JP6: 1x2 2.5mm; PinHeader_1x02_P2.54mm_Vertical
JP9: 1X5 2.5mm; PinHeader_1x04_P2.54mm_Vertical
JPA2, JPA7: 1X3 2.5mm; Molex_SPOX_5267-03A_1x03_P2.50mm_Vertical
JPA3: 1X8 2.5mm; Molex_SPOX_5267-08A_1x08_P2.50mm_Vertical
JPA4: 1X10 2.5mm; Molex_SPOX_5267-10A_1x10_P2.50mm_Vertical
JPA8: 1X5 2.5mm; Molex_SPOX_5267-05A_1x05_P2.50mm_Vertical
JPB2: 1X3 2mm; CONN-TH_3P-P2.00_A2004WV-3P
JPB3: 1X8 2mm; 530140810
JPB4: 1X10 2mm; 530141010
JPB8: 1X5 2mm; CONN-TH_A2004WV-5P
MH1, MH2, MH4: MountingHole_3.2mm
R1, R2: 4K7; R_Axial_DIN0204_L3.6mm_D1.6mm_P2.54mm_Vertical
R3, R4, R5: 150; R_Axial_DIN0204_L3.6mm_D1.6mm_P2.54mm_Vertical
X1: KLDX-0202-AC; BarrelJack_Kycon_KLDX-0202-xC_Horizontal

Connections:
+5V: IC3.6 (~RESET), IC3.18 (VDD), IC4.5 (A0), IC4.6 (~RESET), IC4.18 (VDD), J1.5, JP5.1, JP6.1, JP9.4, JPA2.1, JPA7.1, JPA8.1, JPB2.3, JPB8.5, R1.2, R2.2, R3.1, R4.1, R5.1
+15V: IC1.10 (COM), IC2.10 (COM), JP1.1 (+15V), JPA4.1, JPA4.2, JPB4.1, JPB4.2, X1.2, X1.3
/910_L: J2.10, J4.1, JP5.7
/BUZZ: J2.9, JP6.2
/ENC_A: J4.6, JP5.4, JPA8.4, JPB8.2
/ENC_B: J4.5, JP5.5, JPA8.3, JPB8.3
/ENC_C: J4.4, JP5.6, JPA8.5, JPB8.1
/EOL_L: J3.2, JPA2.3, JPB2.1
/EOL_R: J3.1, JP5.8, JPA7.3
/LED_GRN: D3.1 (K), J4.2
/LED_YEL: D2.1 (K), J4.3
/SCL: IC3.1 (SCL), IC4.1 (SCL), J2.1, J3.6, JP9.2, R1.1
/SDA: IC3.2 (SDA), IC4.2 (SDA), J2.2, J3.5, JP9.3, R2.1
GND: D1.1 (K), IC1.9 (GND), IC2.9 (GND), IC3.3 (A2), IC3.4 (A1), IC3.5 (A0), IC3.9 (VSS), IC4.3 (A2), IC4.4 (A1), IC4.9 (VSS), J1.6, J1.7, J2.4, JP1.2 (GND), JP1.3 (GND), JP5.2, JP5.9, JP5.10, JP9.1, JPA2.2, JPA7.2, JPA8.2, JPB2.2, JPB8.4, X1.1
unnamed: D1.2 (A), R3.2
unnamed: D2.2 (A), R5.2
unnamed: D3.2 (A), R4.2
unnamed: IC1.1 (I1), IC3.10 (GP0)
unnamed: IC1.2 (I2), IC3.11 (GP1)
unnamed: IC1.3 (I3), IC3.12 (GP2)
unnamed: IC1.4 (I4), IC3.13 (GP3)
unnamed: IC1.5 (I5), IC3.14 (GP4)
unnamed: IC1.6 (I6), IC3.15 (GP5)
unnamed: IC1.7 (I7), IC3.16 (GP6)
unnamed: IC1.8 (I8), IC3.17 (GP7)
unnamed: IC1.18 (O1), JPA4.3, JPB4.3
unnamed: IC1.17 (O2), JPA4.4, JPB4.4
unnamed: IC1.16 (O3), JPA4.5, JPB4.5
unnamed: IC1.15 (O4), JPA4.6, JPB4.6
unnamed: IC1.14 (O5), JPA4.7, JPB4.7
unnamed: IC1.13 (O6), JPA4.8, JPB4.8
unnamed: IC1.12 (O7), JPA4.9, JPB4.9
unnamed: IC1.11 (O8), JPA4.10, JPB4.10
unnamed: IC2.1 (I1), IC4.10 (GP0)
unnamed: IC2.2 (I2), IC4.11 (GP1)
unnamed: IC2.3 (I3), IC4.12 (GP2)
unnamed: IC2.4 (I4), IC4.13 (GP3)
unnamed: IC2.5 (I5), IC4.14 (GP4)
unnamed: IC2.6 (I6), IC4.15 (GP5)
unnamed: IC2.7 (I7), IC4.16 (GP6)
unnamed: IC2.8 (I8), IC4.17 (GP7)
unnamed: IC2.18 (O1), JPA3.1, JPB3.1
unnamed: IC2.17 (O2), JPA3.2, JPB3.2
unnamed: IC2.16 (O3), JPA3.3, JPB3.3
unnamed: IC2.15 (O4), JPA3.4, JPB3.4
unnamed: IC2.14 (O5), JPA3.5, JPB3.5
unnamed: IC2.13 (O6), JPA3.6, JPB3.6
unnamed: IC2.12 (O7), JPA3.7, JPB3.7
unnamed: IC2.11 (O8), JPA3.8, JPB3.8

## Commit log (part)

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2025-02-22 Solenoid LED strip
2025-02-22 Move LEDs to be properly on top of solenoids
2025-05-09 Add design file PDFs to repo [skip ci]
2025-05-15 Move polarity symbol to ayab-library

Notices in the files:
ayab-shield/arduino_shield.kicad_pcb:
CC-BY-SA
